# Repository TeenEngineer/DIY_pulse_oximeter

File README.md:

# DIY_pulse_oximeter
Hello! I made this project just as a way to make medical equipment with cheaper components(while retaining quality of the measurements)

# Description
The device uses MAX30102 to measure pulse and SpO2, and the microcontroller is Atmega328p(like the one on arduino nano). I am planning to use a 64x32 0.49" OLED screen to display info, and I also integrated a MCP73831 charging circuit for the battery(planning to use 250mAh tiny li-po), and CH340C for quickly writing firmware. It also used DW01A for over-discharge protection, with FS8205A responsible for cutting off power. And finally, AP2112K-3.3TRG1 supplies 3.3V stable current from the battery.

About assembling the PCB, I am going to order from Aivon(cuz JLCPCB doesn't offer PCBA in my country)

# Schematic, PCB
You can view the schematic and PCB layout **[here](https://kicanvas.org/?repo=https://github.com/TeenEngineer/DIY_pulse_oximeter)**
**OR**
Here is a schematic

# PCB
This is the current layout(in 3D):

# BOM
|Name                                                                  |Price                   |
|----------------------------------------------------------------------|------------------------|
|Bare PCBs 5pcs                                                        |5$                      |
|PCB Assembly for 5pcs                                                 |36$                     |
|Shipping(Fedex, the only cheap option)                                |0$(First order discount)|
|0.49" 64x32 OLED screen(https://ali.click/3mfuk1f, including shipping)|2.68$                   |
|Total                                                                 |44$(in case price of oled goes up                |

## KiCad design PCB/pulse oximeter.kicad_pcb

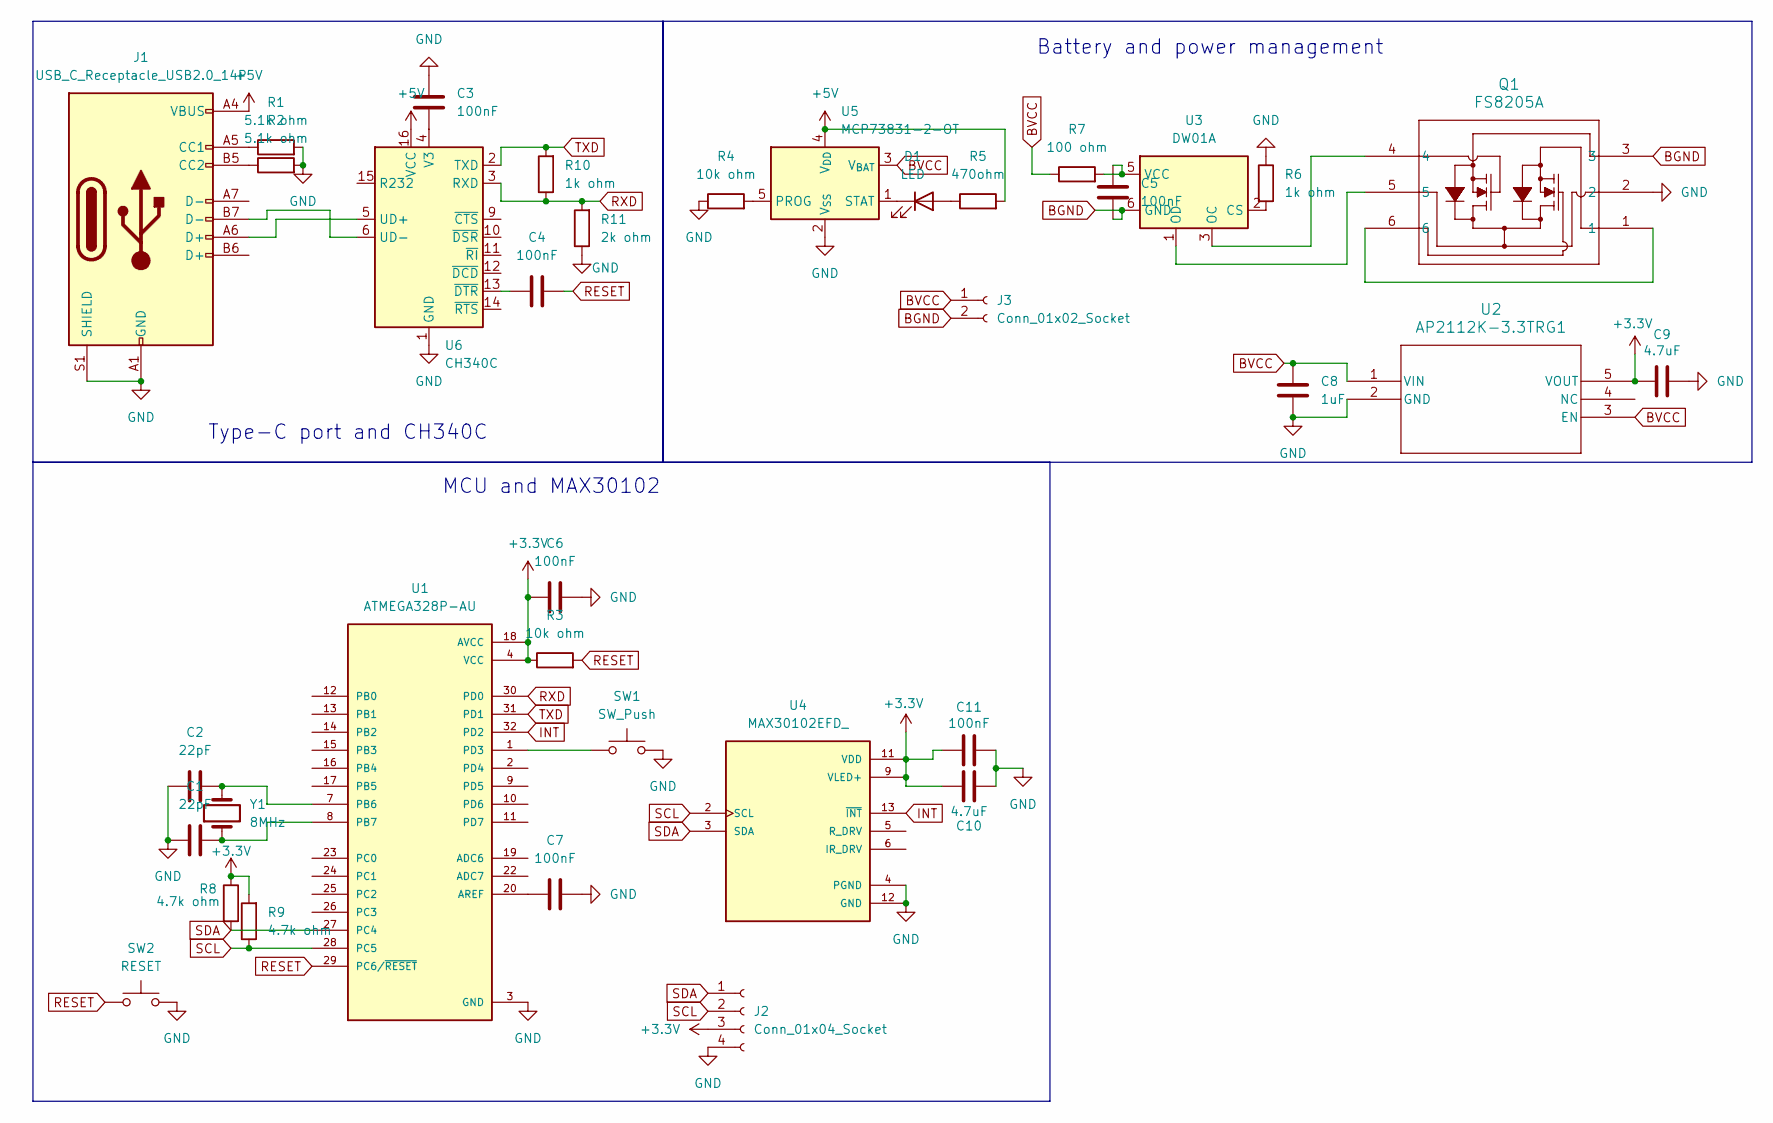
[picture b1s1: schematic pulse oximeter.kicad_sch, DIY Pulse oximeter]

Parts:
C1, C2: 22pF; C_0603_1608Metric; MPN CL10A475KQ8NNNC
C3, C4, C5, C6, C7, C11: 100nF; C_0603_1608Metric; MPN CL10B104KB8NNNC
C8: 1uF; C_0603_1608Metric; MPN C0603C105K9RACAUTO
C9, C10: 4.7uF; C_0603_1608Metric; MPN CL10A475KQ8NNNC
D1: LED; LED_0805_2012Metric; MPN CMD17-21VRD/TR8
J1: USB_C_Receptacle_USB2.0_14P; USB_C_Receptacle_HRO_TYPE-C-31-M-12; MPN 12402012E212A
J2: Conn_01x04_Socket; PinSocket_1x04_P2.54mm_Vertical
J3: Conn_01x02_Socket; JST_PH_S2B-PH-K_1x02_P2.00mm_Horizontal
Q1: FS8205A; SOT-23-6L_TCP; MPN FS8205A
R1, R2: 5.1k ohm; R_0603_1608Metric; MPN FRC0603F5101TS
R3, R4: 10k ohm; R_0603_1608Metric; MPN RC0603FR-0710KL
R5: 470ohm; R_0603_1608Metric; MPN 0603WAF4700T5E
R6, R10: 1k ohm; R_0603_1608Metric; MPN FRC0603F1001TS
R7: 100 ohm; R_0603_1608Metric; MPN Y4021100R000B9W
R8, R9: 4.7k ohm; R_0603_1608Metric; MPN RC0603FR-074K7L
R11: 2k ohm; R_0603_1608Metric; MPN 0603WAF2001T5E
SW1: SW_Push; SW_Push_1P1T_NO_CK_KMR2; MPN KMR641NG ULC LFS
SW2: RESET; SW_Push_1P1T_NO_CK_KMR2; MPN KMR641NG ULC LFS
U1: ATMEGA328P-AU; QFP80P900X900X120-32N; PARTREV 8271A
U2: AP2112K-3.3TRG1; SOT_RG1_DIO; MPN AP2112K-3.3TRG1
U3: DW01A; SOT-23-6; MPN DW01A
U4: MAX30102EFD_; PSON80P330X560X165-14N; PARTREV 0
U5: MCP73831-2-OT; SOT-23-5; MPN MCP73831T-2ACI/OT
U6: CH340C; SOIC127P600X180-16N; MPN CH340C
Y1: 8MHz; Crystal_SMD_3225-4Pin_3.2x2.5mm; MPN X32258MOB4SI

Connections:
+3.3V: C6.1, C9.1, C10.1, C11.1, J2.3, R3.1, R8.1, R9.2, U1.4 (VCC), U1.6 (VCC), U1.18 (AVCC), U2.5 (VOUT), U4.9 (VLED+), U4.10 (VLED+), U4.11 (VDD)
+5V: J1.A4 (VBUS), J1.A9 (VBUS), J1.B4 (VBUS), J1.B9 (VBUS), R5.2, U5.4 (V_{DD}), U6.16 (VCC)
BGND: C5.2, J3.2, Q1.3, U3.6 (GND)
BVCC: C8.1, J3.1, R7.1, U2.1 (VIN), U2.3 (EN), U5.3 (V_{BAT})
GND: C1.1, C2.1, C3.1, C6.2, C7.2, C8.2, C9.2, C10.2, C11.2, J1.A1 (GND), J1.A12 (GND), J1.B1 (GND), J1.B12 (GND), J1.S1 (SHIELD), J2.4, Q1.2, R1.2, R2.2, R4.1, R6.1, R11.1, SW1.2, SW2.2, U1.3 (GND), U1.5 (GND), U1.21 (GND), U2.2 (GND), U4.4 (PGND), U4.12 (GND), U5.2 (V_{SS}), U6.1 (GND)
INT: U1.32 (PD2), U4.13 (~INT)
unnamed: D1.2 (A), R5.1
unnamed: D1.1 (K), U5.1 (STAT)
unnamed: J1.A5 (CC1), R1.1
unnamed: J1.B5 (CC2), R2.1
unnamed: Q1.1, Q1.6
unnamed: C7.1, U1.20 (AREF)
unnamed: C2.2, U1.7 (PB6), Y1.2
unnamed: C1.2, U1.8 (PB7), Y1.1
unnamed: SW1.1, U1.1 (PD3)
unnamed: R6.2, U3.2 (CS)
unnamed: Q1.4, U3.3 (OC)
unnamed: Q1.5, U3.1 (OD)
unnamed: C5.1, R7.2, U3.5 (VCC)
unnamed: R4.2, U5.5 (PROG)
unnamed: J1.A6 (D+), U6.5 (UD+)
unnamed: J1.B7 (D-), U6.6 (UD-)
unnamed: C3.2, U6.4 (V3)
unnamed: C4.2, U6.13 (~DTR)
RESET: C4.1, R3.2, SW2.1, U1.29 (PC6/~RESET)
RXD: R10.1, R11.2, U1.30 (PD0), U6.3 (RXD)
SCL: J2.2, R9.1, U1.28 (PC5), U4.2 (SCL)
SDA: J2.1, R8.2, U1.27 (PC4), U4.3 (SDA)
TXD: R10.2, U1.31 (PD1), U6.2 (TXD)

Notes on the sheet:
Battery and power management
MCU and MAX30102
Type-C port and CH340C

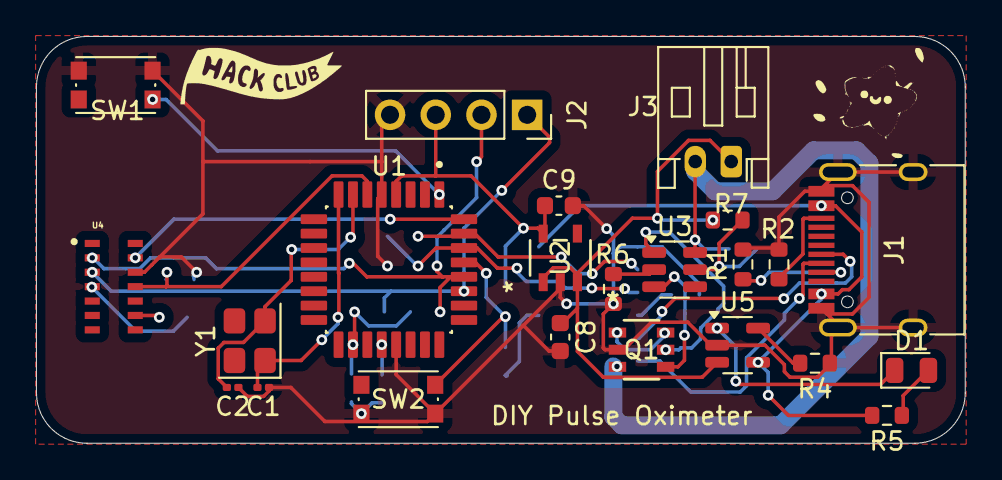
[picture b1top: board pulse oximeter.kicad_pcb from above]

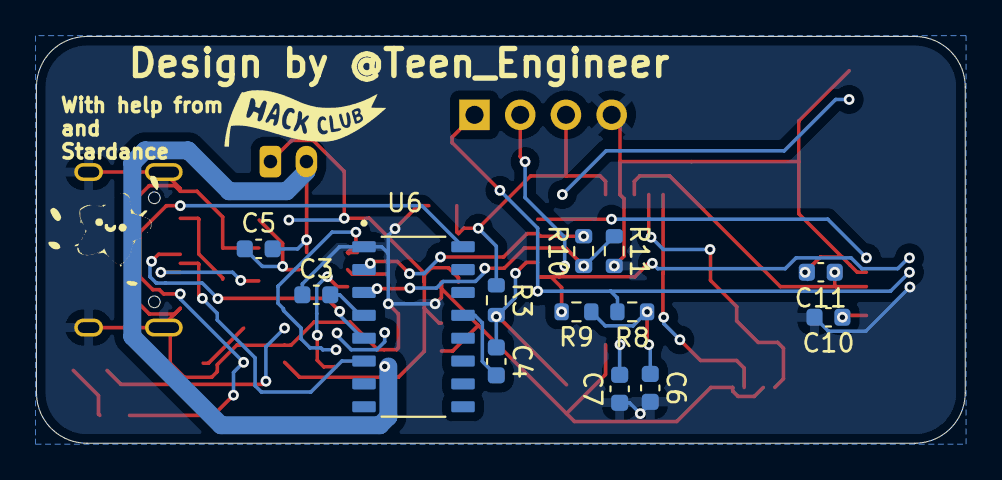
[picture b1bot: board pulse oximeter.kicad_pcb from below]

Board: 2 copper layers, 51.6 x 22.6 mm, 40 parts (15 on the bottom side), 29 nets.

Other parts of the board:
., .#2: LOGO
 : LOGO
 #2: LOGO

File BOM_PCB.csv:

"Reference","Qty","Value","DNP","Exclude from BOM","Exclude from Board","Footprint","Datasheet","MPN"
"C1,C2","2","22pF","","","","Capacitor_SMD:C_0603_1608Metric","~","CL10A475KQ8NNNC"
"C3,C4,C5,C6,C7,C11","6","100nF","","","","Capacitor_SMD:C_0603_1608Metric","~","CL10B104KB8NNNC"
"C8","1","1uF","","","","Capacitor_SMD:C_0603_1608Metric","~","C0603C105K9RACAUTO"
"C9,C10","2","4.7uF","","","","Capacitor_SMD:C_0603_1608Metric","~","CL10A475KQ8NNNC"
"D1","1","LED","","","","LED_SMD:LED_0805_2012Metric","~","CMD17-21VRD/TR8"
"J1","1","USB_C_Receptacle_USB2.0_14P","","","","Connector_USB:USB_C_Receptacle_HRO_TYPE-C-31-M-12","https://www.usb.org/sites/default/files/documents/usb_type-c.zip","12402012E212A"
"J2","1","Conn_01x04_Socket","","","","Connector_PinSocket_2.54mm:PinSocket_1x04_P2.54mm_Vertical","~",""
"J3","1","Conn_01x02_Socket","","","","Connector_JST:JST_PH_S2B-PH-K_1x02_P2.00mm_Horizontal","~",""
"Q1","1","FS8205A","","","","fs8205:SOT-23-6L_TCP","FS8205A","FS8205A"
"R1,R2","2","5.1k ohm","","","","Resistor_SMD:R_0603_1608Metric","~","FRC0603F5101TS"
"R3,R4","2","10k ohm","","","","Resistor_SMD:R_0603_1608Metric","~","RC0603FR-0710KL"
"R5","1","470ohm","","","","Resistor_SMD:R_0603_1608Metric","~","0603WAF4700T5E"
"R6,R10","2","1k ohm","","","","Resistor_SMD:R_0603_1608Metric","~"," FRC0603F1001TS,FRC0603F1001TS"
"R7","1","100 ohm","","","","Resistor_SMD:R_0603_1608Metric","~","Y4021100R000B9W"
"R8,R9","2","4.7k ohm","","","","Resistor_SMD:R_0603_1608Metric","~","RC0603FR-074K7L"
"R11","1","2k ohm","","","","Resistor_SMD:R_0603_1608Metric","~","0603WAF2001T5E"
"SW1","1","SW_Push","","","","Button_Switch_SMD:SW_Push_1P1T_NO_CK_KMR2","~","KMR641NG ULC LFS"
"SW2","1","RESET","","","","Button_Switch_SMD:SW_Push_1P1T_NO_CK_KMR2","~","KMR641NG ULC LFS"
"U1","1","ATMEGA328P-AU","","","","ATMEGA328P-AU:QFP80P900X900X120-32N","","ATMEGA328P-AU"
"U2","1","AP2112K-3.3TRG1","","","","ap2112k:SOT_RG1_DIO","AP2112K-3.3TRG1","AP2112K-3.3TRG1"
"U3","1","DW01A","","","","Package_TO_SOT_SMD:SOT-23-6","https://hmsemi.com/downfile/DW01A.PDF","DW01A"
"U4","1","MAX30102EFD_","","","","MAX30102EFD_:PSON80P330X560X165-14N","","MAX30102EFD+"
"U5","1","MCP73831-2-OT","","","","Package_TO_SOT_SMD:SOT-23-5","http://ww1.microchip.com/downloads/en/DeviceDoc/20001984g.pdf","MCP73831T-2ACI/OT"
"U6","1","CH340C","","","","CH340C:SOIC127P600X180-16N","https://datasheet.lcsc.com/szlcsc/Jiangsu-Qin-Heng-CH340C_C8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","CH340C"
"Y1","1","8MHz","","","","Crystal:Crystal_SMD_3225-4Pin_3.2x2.5mm","~"," X32258MOB4SI"
